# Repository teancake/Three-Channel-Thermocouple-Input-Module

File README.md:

# Three-Channel Thermocouple Input Module (K Type) #
This repository includes the schematic and PCB design of a three-channel thermocouple input module (K-type). This module is similar to the [Adafruit thermocouple amplifier breakout board](https://www.adafruit.com/product/269), but allowing for three channels of input. This module (or breakout board) also uses MAX6675 chip and can only be connected to [K-type thermocouples](https://www.adafruit.com/products/270). MAX6675 can sense temperatures ranging from 0 to 1024 Degrees Celcius.

## Dimensions: ##
Length: 45mm/1.77in
Width: 28mm/1.1in

## Data Interface ##
The MAX6675 chip uses an SPI-compatible serial interface (only SCK and MISO). 

## Arduino Library ##
The [MAX6675 library from Adafruit](https://github.com/adafruit/MAX6675-library) can be readily used.

## The Finished Board ##

* Note that there are no 3.3V voltage regulators on this board. The MAX6675 chip itself accepts both 3.3V and 5V power input, but make sure the voltage level of the I/O pins are compatible with the devices connected. *

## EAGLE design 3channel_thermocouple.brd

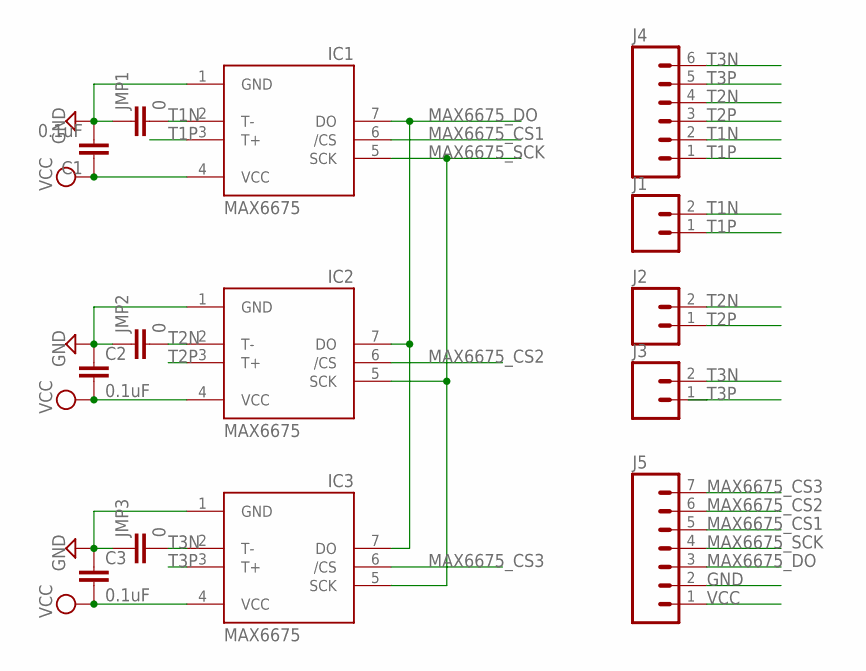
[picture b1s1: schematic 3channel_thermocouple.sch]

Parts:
C1, C2, C3: 0.1uF; 0603-CAP
IC1, IC2, IC3: MAX6675; SO08
J1, J2, J3: M025MM; SCREWTERMINAL-5MM-2
J4: M06; 1X6-XH-JST-S6B-RIGHTANGLE
J5: M07; 1X07
JMP1, JMP2, JMP3: 0; 0603-CAP

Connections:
GND: C1.2, C2.1, C3.1, IC1.1 (GND), IC2.1 (GND), IC3.1 (GND), J5.2, JMP1.1, JMP2.1, JMP3.1
MAX6675_CS1: IC1.6 (/CS), J5.5
MAX6675_CS2: IC2.6 (/CS), J5.6
MAX6675_CS3: IC3.6 (/CS), J5.7
MAX6675_DO: IC1.7 (DO), IC2.7 (DO), IC3.7 (DO), J5.3
MAX6675_SCK: IC1.5 (SCK), IC2.5 (SCK), IC3.5 (SCK), J5.4
T1N: IC1.2 (T-), J1.2, J4.2, JMP1.2
T1P: IC1.3 (T+), J1.1, J4.1
T2N: IC2.2 (T-), J2.2, J4.4, JMP2.2
T2P: IC2.3 (T+), J2.1, J4.3
T3N: IC3.2 (T-), J3.2, J4.6, JMP3.2
T3P: IC3.3 (T+), J3.1, J4.5
VCC: C1.1, C2.2, C3.2, IC1.4 (VCC), IC2.4 (VCC), IC3.4 (VCC), J5.1

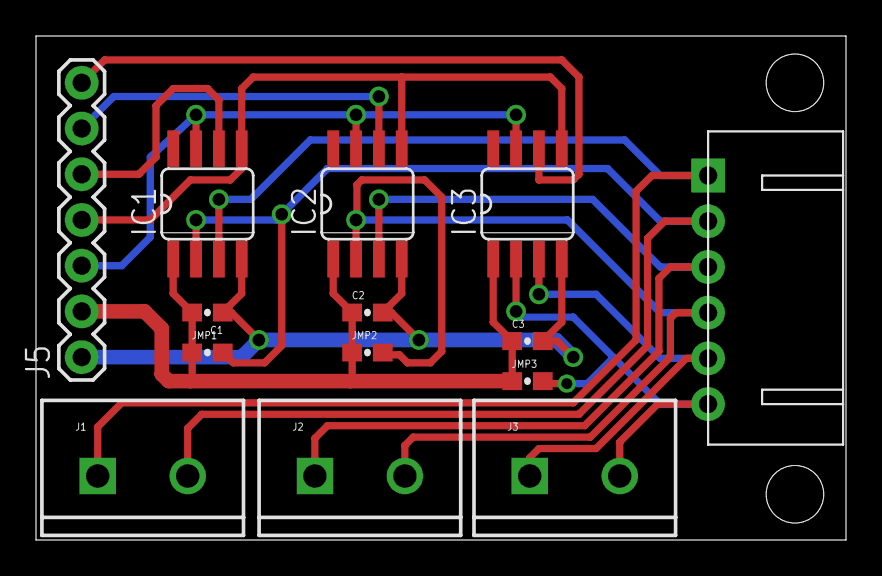
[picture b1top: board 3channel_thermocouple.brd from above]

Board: 2 copper layers, 45.0 x 28.0 mm, 14 parts (0 on the bottom side), 13 nets.

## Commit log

2016-12-14 all design files.
2016-12-14 images of the finished board
